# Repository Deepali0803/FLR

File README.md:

# FLR--Flight-Computer
There are numerous flight computers available in the market. My goal was to design a flight computer with components that have reasonably low pricing to reduce the overall production cost, available in breakout boards, and widely available.

This Flight Computer for Landing Model Rocket is capable of:
1. Calculating Orientation
2. Calculating Altitude
3. Controlling pyros for deploying parachute and landing legs
4. Controlling two servo motors
5. Logging flight data
6. Accessing flight data

=> For orientation sensing on the rocket, IMU - Inertial Measurement Unit MPU-6050 is used with a built-in gyroscope and an accelerometer sensor.

=> For altitude sensing, BMP280 Barometric Pressure Sensor is used which measures the atmospheric density of the air surrounding it and it gets lower as you get higher up into the atmosphere. By measuring the change in atmospheric density we determine how high the rocket is above the ground.

=> N-channel mosfets are used to control parachutes, landing-like deployments, and firing motors.

=> Main brain of the computer is the widely available Atmega328 processor.

=> To log and access the flight data, SPI - Serial Peripheral Interface flash chip is used along with MicroSD Card.

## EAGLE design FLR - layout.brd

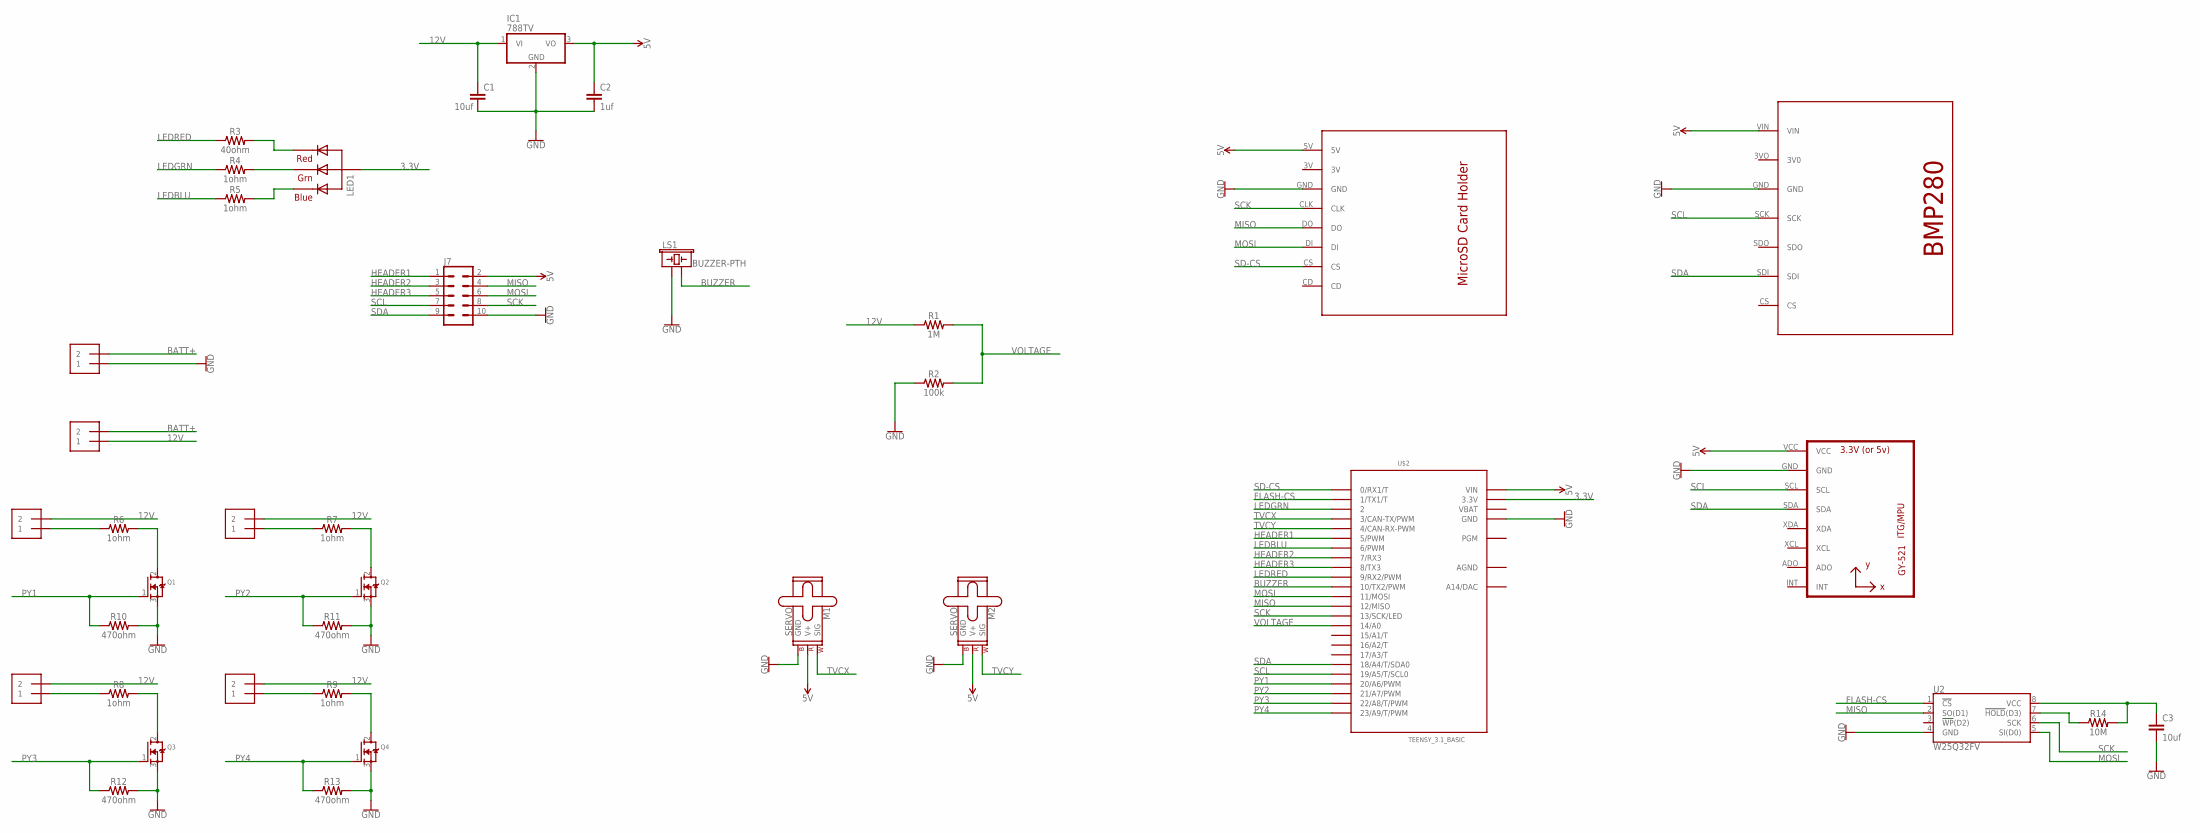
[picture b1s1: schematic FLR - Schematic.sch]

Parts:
C1, C3: 10uf; CAP-PTH-2.54
C2: 1uf; CAP-PTH-2.54
IC1: 788TV; TO220V
J1, J2, J3, J4, J5, J6: 1X2-3.5MM
J7: CONN_05X2NO_SILK; 2X5_NOSILK
LED1: RGBLED_CA-5MM; LED5MMRGB
LS1: BUZZER-PTH; BUZZER-12MM
M1, M2: SERVO; 1X03
Q1, Q2, Q3, Q4: MOSFET-NGDS_TO220V; TO220V
R1: 1M; AXIAL-0.3
R2: 100k; AXIAL-0.3
R3: 40ohm; AXIAL-0.3
R4, R5, R6, R7, R8, R9: 1ohm; AXIAL-0.3
R10, R11, R12, R13: 470ohm; AXIAL-0.3
R14: 10M; AXIAL-0.3
U1: GY-521MPU6050; GY-521
U2: W25Q32FV; SOIC-8
U$1: MICROSDCARD
U$2: TEENSY_3.1_BASIC
U$3: BMP280

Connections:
3.3V: LED1.2 (VCC), U$2.3.3V, U$2.3.3V1 (3.3V)
5V: C2.1, IC1.3 (VO), J7.2, M1.2 (V+), M2.2 (V+), U1.VCC, U$1.5V, U$2.VIN, U$3.VIN
12V: C1.1, IC1.1 (VI), J2.1, J3.2, J4.2, J5.2, J6.2, R1.P$1 (1)
AGND: U$2.AGND
BATT+: J1.2, J2.2
BUZZER: LS1.- (2), U$2.10 (10/TX2/PWM)
FLASH-CS: U2.1 (!CS!), U$2.1 (1/TX1/T)
GND: C1.2, C2.2, C3.2, IC1.2 (GND), J1.1, J7.10, LS1.+ (1), M1.3 (GND), M2.3 (GND), Q1.3 (S), Q2.3 (S), Q3.3 (S), Q4.3 (S), R2.P$1 (1), R10.P$2 (2), R11.P$2 (2), R12.P$2 (2), R13.P$2 (2), U1.GND, U2.4 (GND), U$1.GND, U$2.GND, U$2.GND1 (GND), U$3.GND
HEADER1: J7.1, U$2.5 (5/PWM)
HEADER2: J7.3, U$2.7 (7/RX3)
HEADER3: J7.5, U$2.8 (8/TX3)
LEDBLU: R5.P$1 (1), U$2.6 (6/PWM)
LEDGRN: R4.P$1 (1), U$2.2
LEDRED: R3.P$1 (1), U$2.9 (9/RX2/PWM)
MISO: J7.4, U2.2 (SO(D1)), U$1.DO, U$2.12 (12/MISO)
MOSI: J7.6, U2.5 (SI(D0)), U$1.DI, U$2.11 (11/MOSI)
unnamed: Q1.2 (D), R6.P$2 (2)
unnamed: LED1.1 (RED), R3.P$2 (2)
unnamed: LED1.3 (GREEN), R4.P$2 (2)
unnamed: LED1.4 (BLUE), R5.P$2 (2)
unnamed: J3.1, R6.P$1 (1)
unnamed: Q2.2 (D), R7.P$2 (2)
unnamed: J4.1, R7.P$1 (1)
unnamed: Q3.2 (D), R8.P$2 (2)
unnamed: J5.1, R8.P$1 (1)
unnamed: Q4.2 (D), R9.P$2 (2)
unnamed: J6.1, R9.P$1 (1)
unnamed: C3.1, R14.P$2 (2), U2.8 (VCC)
unnamed: R14.P$1 (1), U2.7 (!HOLD!(D3))
PY1: Q1.1 (G), R10.P$1 (1), U$2.20/A6 (20/A6/PWM)
PY2: Q2.1 (G), R11.P$1 (1), U$2.21/A7 (21/A7/PWM)
PY3: Q3.1 (G), R12.P$1 (1), U$2.22/A8 (22/A8/T/PWM)
PY4: Q4.1 (G), R13.P$1 (1), U$2.23/A9 (23/A9/T/PWM)
SCK: J7.8, U2.6 (SCK), U$1.CLK, U$2.13 (13/SCK/LED)
SCL: J7.7, U1.SCL, U$2.19/A5 (19/A5/T/SCL0), U$3.SCK
SD-CS: U$1.CS, U$2.0 (0/RX1/T)
SDA: J7.9, U1.SDA, U$2.18/A4 (18/A4/T/SDA0), U$3.SDI
TVCX: M1.1 (SIG), U$2.3 (3/CAN-TX/PWM)
TVCY: M2.1 (SIG), U$2.4 (4/CAN-RX-PWM)
VBAT: U$2.VBAT
VOLTAGE: R1.P$2 (2), R2.P$2 (2), U$2.14/A0

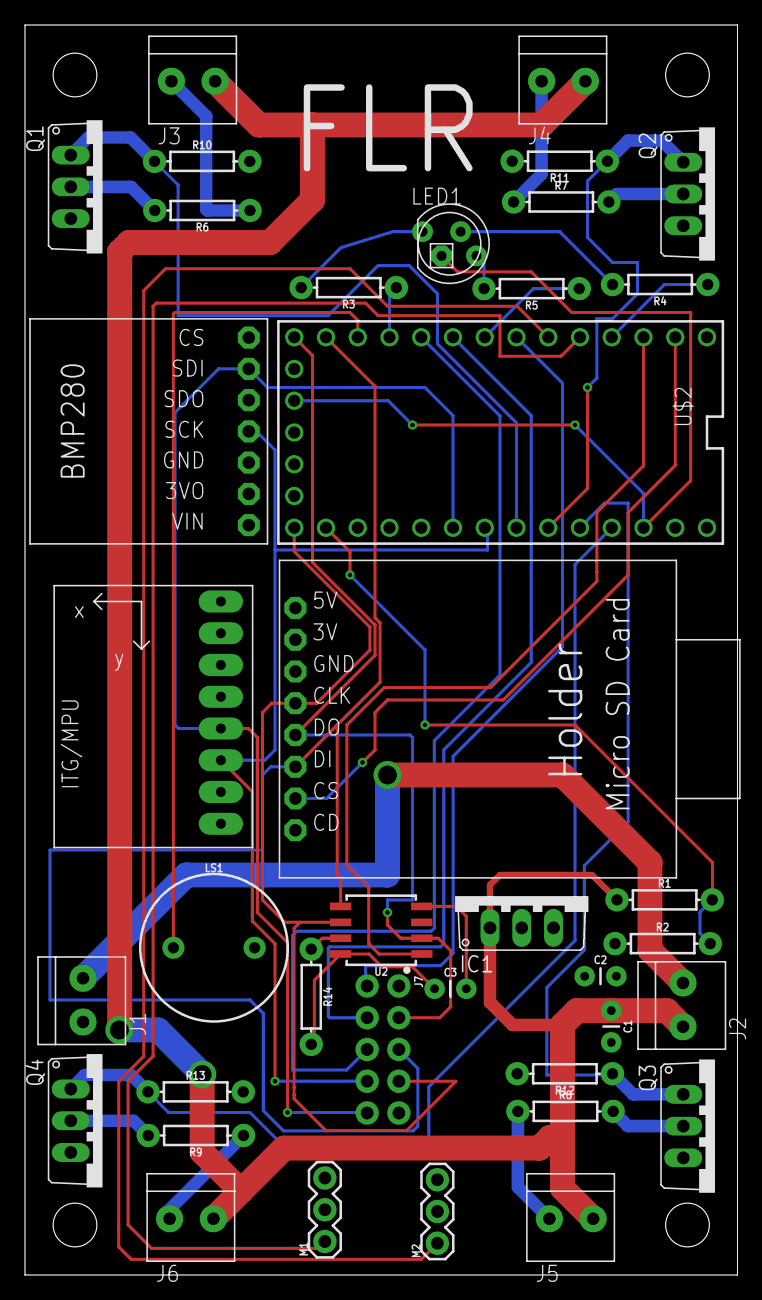
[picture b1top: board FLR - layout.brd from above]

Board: 2 copper layers, 57.0 x 100.0 mm, 38 parts (0 on the bottom side), 39 nets.

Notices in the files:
parts and their libraries:
SparkFun-PowerSymbols: Licensing: Creative Commons ShareAlike 4.0 International - https://creativecommons.org/licenses/by-sa/4.0
